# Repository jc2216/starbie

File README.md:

## Starbie
A tiny motion-controlled digital pet, built for HackClub Halflife because I really want a 3D printer and also because I want to get better at electronics since I am an absolute noob.
I added a buzzer so that twinkle twinkle little star plays when the sprite is napping. I also added a rain animation when the humidity is greater than a certain threshold. We'll see if that works. 

Next Steps: 
* Change up some of the animations.
* implement sound during other actions/when using the selection thing.

---
## Features
* 1 XIAO ESP-32 C3 Microcontroller
* 2 Push buttons
* 1 MPU6050 IMU
* 1 DHT11 Environment Sensor
* 1 OLED Display

This starbie has a display with a sprite. The sprite has 3 values: joy, energy, and fullness. These three values change depending on the actions it does, such as whether it is napping or playing. Additionally, there are some neat animations, like some with hearts and sparkles. 

## Process
1. Designed the Schematic. This wasn't too hard since it was just following the Starbie guide for the most part. The buttons are wired to the ESP-32 through some of the pins, and so is the OLED, MPU6050, environment sensor, and the buzzer that I added. They are also all wired to GND. 

2. PCB routing. This was really annoying to do since there were some cases when I did half of the routing, but the other half was impossible to do, so I had to do it all over again. I also had to redo the PCB routing when I added the buzzer, so that was really annoying, too. Some things I learned are vias, which allow you to switch between the front and back copper layer, and ground pours, which you could draw by adding a board outline. The layout was done similar to the guide, which I assume tried to minimize the rat's nest. 

3. Firmware! I added sparkles like in the guide, and I also created my own sprite using Clip Studio Paint. Some new features that I have added to the firmware is a rain animation when the humidity that the Environment Sensor detects is over a certain amount and a buzzer that plays twinkle twinkle little star when the sprite is napping. I had a pitches.h file that I copy pasted from somewhere since it just contained the default values for each note, and I also had a rain_frames.h file that I got from oledanimationmaker. In my main code, I had an array containing the notes and a parallel array containing the durations that correspond to each note. 

4. Building + Uploading Firmware. I haven't gotten to this step yet, but I am pretty sure that you connect a USB cable from the ESP-32 to your computer. Then, in the Arduino IDE, you can verify the code with the check button, and then upload it with the arrow pointing right button. As for assembling the PCB, it will probably have some soldering involved, which I don't know how to do yet because I am an absolute beginner at PCBs. 

## BOM
| Part | Qty | Unit | Total | Vendor |
|:-----|----:|-----:|------:|:-------|
| XIAO ESP32-C3 | 1 | $4.99 | $4.99 | Seeed Studio |
| 0.96" OLED | 1 | $2.78 | $2.78 | AliExpress |
| MPU6050 | 1 | $2.10 | $2.10 | AliExpress |
| DHT11 | 1 | $1.05 | $1.05 | AliExpress |
| MX Switches | 4 | $0.05 | $0.20 | AliExpress |
| Keycaps | 1 | $0.01 | $0.01 | AliExpress |
| 10k Resistor | 1 | $0.05 | $0.05 | Amazon |
| PCB | 1 | $9.20 | $9.20 | JLCPCB |
| Passive piezo buzzer | 1 | $0.64 | $0.64 | AliExpress |
| **Total** | | | **$21.02** | |

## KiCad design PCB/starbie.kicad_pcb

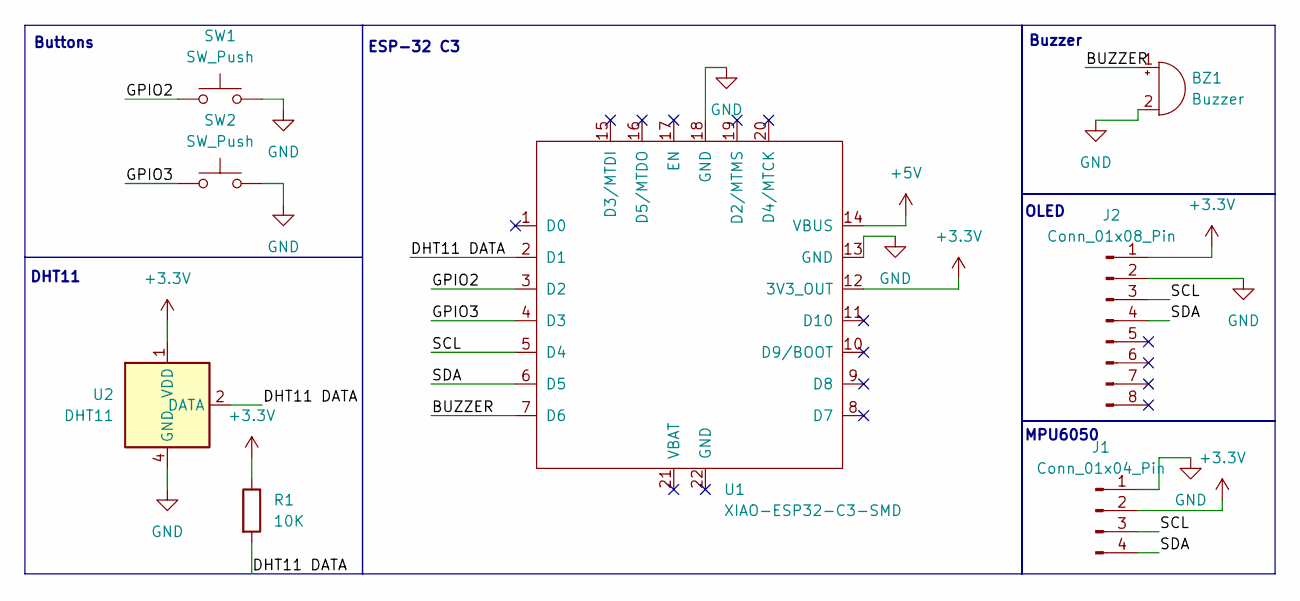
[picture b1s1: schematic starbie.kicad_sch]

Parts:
BZ1: Buzzer; Buzzer_TDK_PS1240P02BT_D12.2mm_H6.5mm
J1: Conn_01x04_Pin; Display_128x64_096_I2C
J2: Conn_01x08_Pin; PinHeader_1x08_P2.54mm_Vertical
R1: 10K; R_Axial_DIN0204_L3.6mm_D1.6mm_P7.62mm_Horizontal
SW1, SW2: SW_Push; SW_Cherry_MX_1.00u_PCB
U1: XIAO-ESP32-C3-SMD
U2: DHT11; Aosong_DHT11_5.5x12.0_P2.54mm

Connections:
+3.3V: J1.2, J2.1, R1.1, U1.12 (3V3_OUT), U2.1 (VDD)
+5V: U1.14 (VBUS)
/BUZZER: BZ1.1 (+), U1.7 (D6)
/DHT11 DATA: R1.2, U1.2 (D1), U2.2 (DATA)
/GPIO2: SW1.1, U1.3 (D2)
/GPIO3: SW2.1, U1.4 (D3)
/SCL: J1.3, J2.3, U1.5 (D4)
/SDA: J1.4, J2.4, U1.6 (D5)
GND: BZ1.2 (-), J1.1, J2.2, SW1.2, SW2.2, U1.13 (GND), U1.18 (GND), U2.4 (GND)

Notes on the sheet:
ESP-32 C3
DHT11
OLED
MPU6050
Buttons
Buzzer

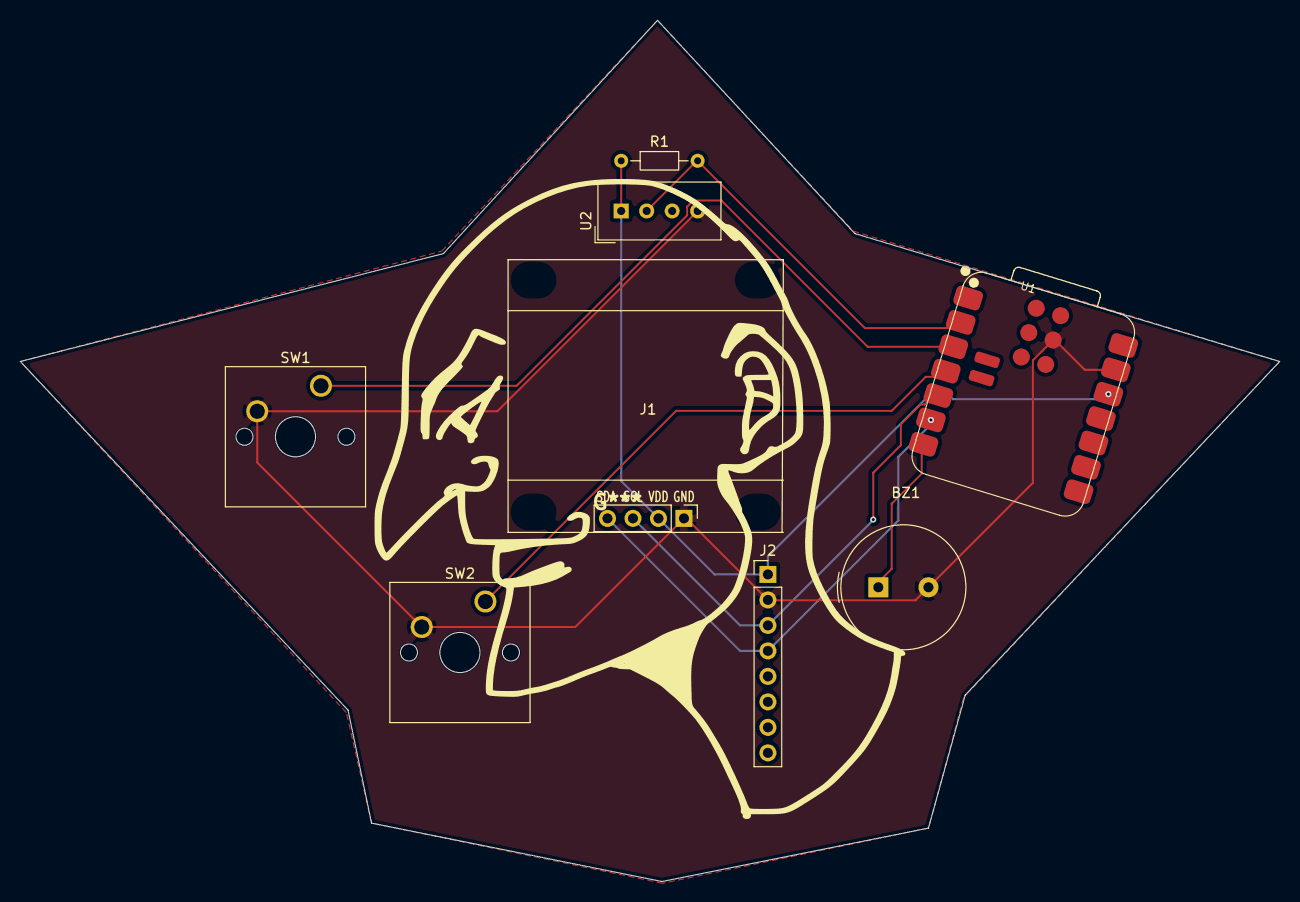
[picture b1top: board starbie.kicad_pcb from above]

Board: 2 copper layers, 125.5 x 85.8 mm, 8 parts (0 on the bottom side), 8 nets.
